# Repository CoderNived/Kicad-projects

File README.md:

# ⚡ Power Chain Build Guide

This guide walks you through building a basic **AC → DC power chain** with a bridge rectifier, filter capacitor, voltage regulator, and load.  
Mentors will check your circuit with a multimeter (DMM) and oscilloscope (DSO).  

---

## 📝 Step A — Plan (5 minutes)

1. **Choose your regulator:**
   - `7805` → Fixed 5 V output (simple, common).
   - `LM317` → Adjustable output (needs resistors).
   - Switching module → More efficient (if allowed).

2. **Prepare heatsink:**  
   - For `7805`, attach a heatsink if current > 100 mA.

3. **Select test load:**
   - `33 Ω, 5 W` → ~150 mA load.
   - `16 Ω, 5 W` → ~300 mA load.
   - Add an **LED + 330 Ω resistor** in parallel as a power indicator.

---

## 🔌 Step B — Build Rectifier

1. **Using bridge rectifier IC (easy):**
   - Connect AC wires to the `~ ~` pins.
   - `+` = DC positive, `-` = DC negative/ground.

2. **Using 4 diodes (manual bridge):**
   - Arrange 4 diodes in a diamond.
   - AC input to two opposite corners.
   - Remaining corners = +DC and -DC.
   - Stripe side of diode (cathode) points to positive node.

---

## 🛢️ Step C — Add Bulk Filter

1. Connect a **large electrolytic capacitor** (10,000 µF, 25 V) across DC + and DC –.  
   - Long leg = positive.  
   - Short leg = negative (ground).  
   ⚠️ Check polarity carefully.

2. Add a **0.1 µF ceramic capacitor** in parallel (filters high-frequency noise).

3. Add a **100 kΩ, 1 W resistor** across the capacitor (bleeder) so it discharges safely after power-off.

---

## 🎚️ Step D — Voltage Regulator

1. Connect DC + to **regulator IN**, DC – to **GND**.  
2. Take regulated voltage from **OUT**.  
3. Add capacitors close to pins:
   - Input side: 0.33 µF (ceramic) + 10 µF (electrolytic).
   - Output side: 0.1 µF (ceramic) + 10 µF (electrolytic).
4. Attach heatsink if load >100 mA.

---

## 💡 Step E — Load & Indicators

1. Connect **33 Ω, 5 W resistor** across +5 V and GND (dummy load).  
   - Use **16 Ω, 5 W** for higher current (~300 mA).  

2. Connect **LED + 330 Ω resistor** in parallel as a visual "power ON" indicator.  

3. Verify:
   - **Multimeter (DMM):** Output should be ~5.0 V.  
   - **Oscilloscope (DSO):**
     - At capacitor: ripple (sawtooth at 100 Hz).  
     - At regulator output: flat line with <50 mV ripple.  

---

## ✅ Quick Recap Flow

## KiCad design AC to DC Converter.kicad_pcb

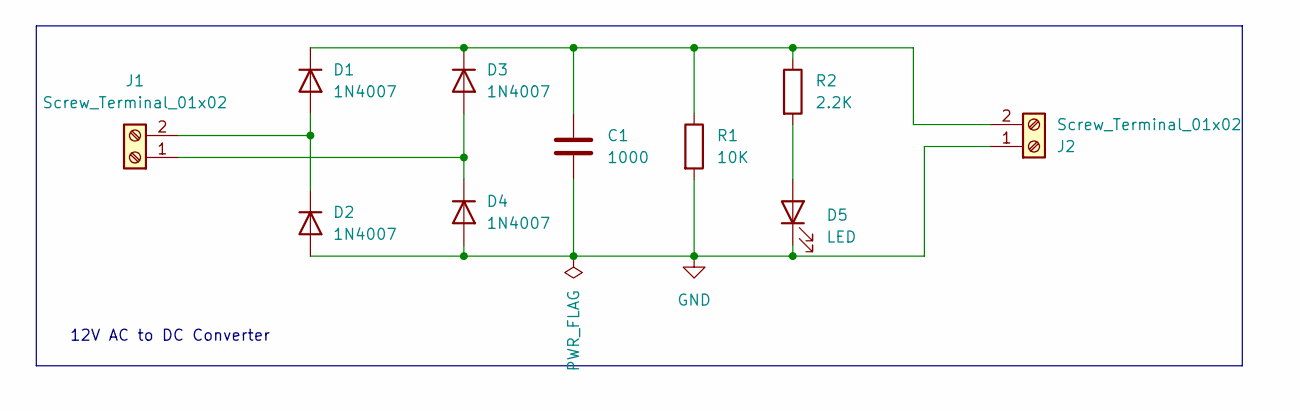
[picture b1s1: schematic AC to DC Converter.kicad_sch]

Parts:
C1: 1000; CP_Radial_D8.0mm_P2.50mm
D1, D2, D3, D4: 1N4007; D_DO-41_SOD81_P10.16mm_Horizontal
D5: LED; LED_D5.0mm
J1, J2: Screw_Terminal_01x02; TerminalBlock_bornier-2_P5.08mm
R1: 10K; R_Axial_DIN0204_L3.6mm_D1.6mm_P7.62mm_Horizontal
R2: 2.2K; R_Axial_DIN0204_L3.6mm_D1.6mm_P7.62mm_Horizontal

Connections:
GND: C1.2, D2.2 (A), D4.2 (A), D5.1 (K), J2.1, R1.2
unnamed: D1.2 (A), D2.1 (K), J1.2
unnamed: C1.1, D1.1 (K), D3.1 (K), J2.2, R1.1, R2.1
unnamed: D3.2 (A), D4.1 (K), J1.1
unnamed: D5.2 (A), R2.2

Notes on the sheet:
12V AC to DC Converter

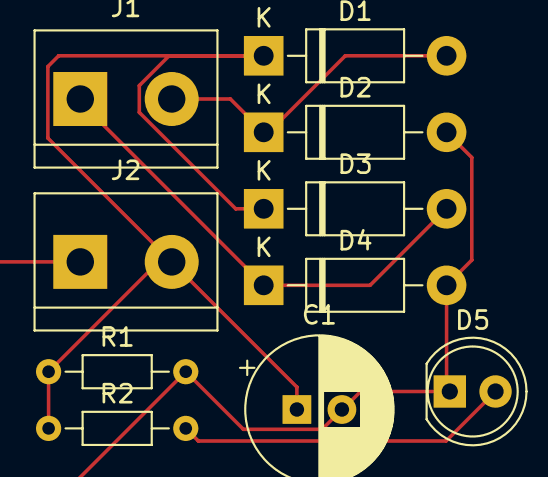
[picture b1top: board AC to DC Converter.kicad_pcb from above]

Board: 2 copper layers, 10 parts (0 on the bottom side), 5 nets.

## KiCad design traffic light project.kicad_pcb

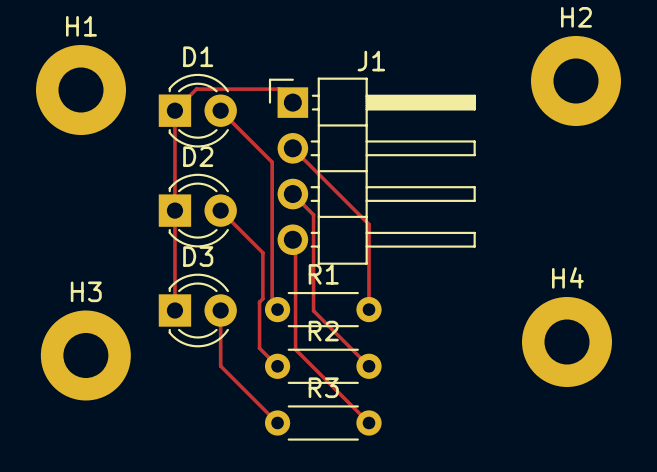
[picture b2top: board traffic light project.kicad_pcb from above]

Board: 2 copper layers, 11 parts (0 on the bottom side), 7 nets.

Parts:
D1, D2, D3: LED; LED_D3.0mm
H1, H2, H3, H4: MountingHole; MountingHole_2.5mm_Pad
J1: Conn_01x04; PinHeader_1x04_P2.54mm_Horizontal
R1, R2, R3: R; R_Axial_DIN0204_L3.6mm_D1.6mm_P5.08mm_Horizontal

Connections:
unnamed: D1.2 (A), R1.1
unnamed: D1.1 (K), D2.1 (K), D3.1 (K), J1.1
unnamed: D2.2 (A), R2.1
unnamed: D3.2 (A), R3.1
unnamed: J1.2, R1.2
unnamed: J1.3, R2.2
unnamed: J1.4, R3.2

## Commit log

2025-03-13 Add files via upload
    traffic light project
2025-03-17 Create AC to Dc converter
2025-03-17 Create Transformerless power supply
2025-03-17 Create Servo motor tester
2025-03-17 Create DC motor speed controller
2025-03-17 Rename AC to Dc converter to AC to DC Converter
2025-03-17 Create USB to UART converter
